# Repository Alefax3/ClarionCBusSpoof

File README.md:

# ClarionC-Blue
Clarion C-Bus interface made with arduino to spoof CD changer. Targeted use is for bluetooth, could also be simplified and used for AUX IN. The end goal is to have a single package Bluetooth module that plugs in to the CD Changer cable in the trunk and provides plug and play for bluetooth audio from a mobile phone or music device.

### Support

Testing and initial application being done in a 1995 Saab 900 S with stock head unit and existing CD changer wiring. Will work with any new generation Saab 900 from 1994 to 1998 (Excluding 1994 convertible).

Theory indicates that this unit, when assembled, will work with any Clarion made stereo using the 13 pin DIN connector as a CD changer interface. I do not have the ability to test with any other units. The only unit available to me, and the only unit I target, is the factory Clarion unit installed in my Saab 900.

This device is not planned at this time to support bluetooth hands free. It will only support A2DP (stereo audio) and AVRCP (playback controls).

The first prototype of the device will display mock track time on display, and persistent CD 1 TRACK 1, but it will not display track information. That is in the wish list, but the main goal here first is to establish communications between the device and the head unit.

### Documentation
http://embedded-bg.com/clarion_c-bus.txt

This document was incredibly insightful in regards to the protocols Clarion is using to communicate between the head and changer.

### Components
Component list will be published when a prototype has been built.

### Licensing
OPEN SOURCE BABY.

GNU General Public License, version 2.0 (GPL-2.0)

https://opensource.org/licenses/GPL-2.0

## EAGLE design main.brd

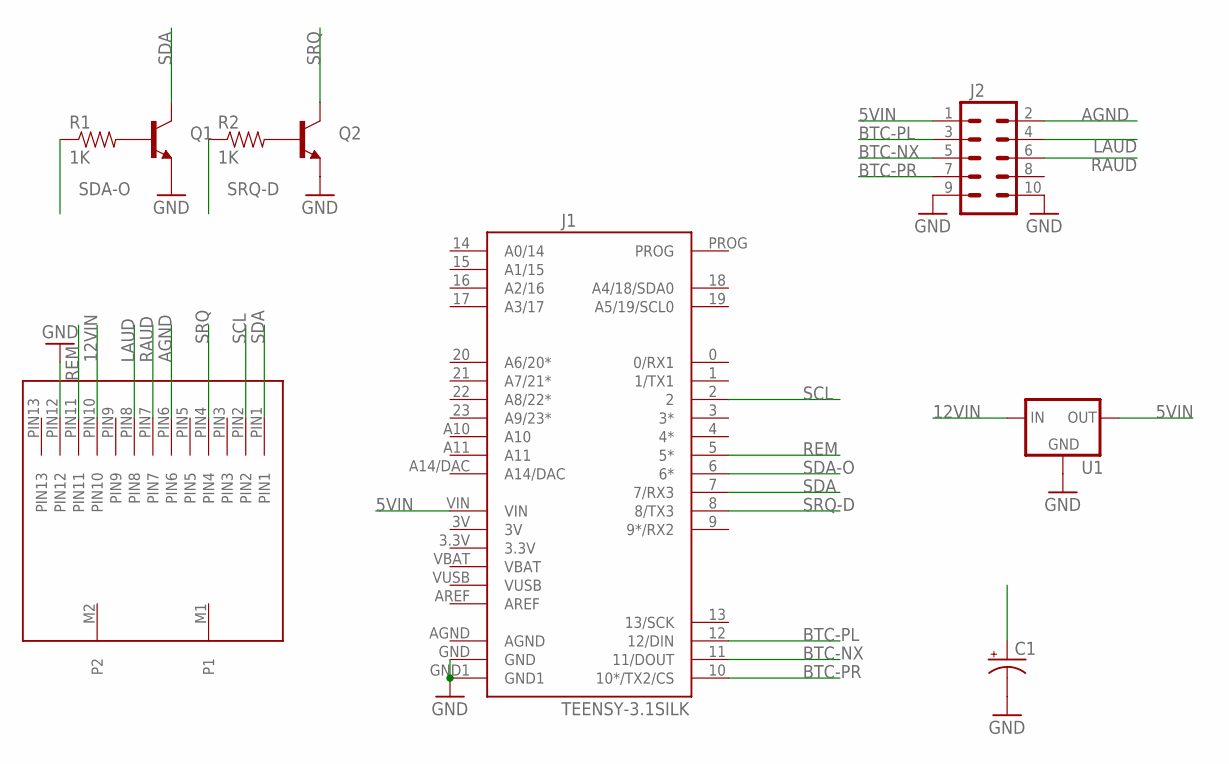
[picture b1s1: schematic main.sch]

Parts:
C1: 10UF-25V-20%(PTH); CPOL-RADIAL-10UF-25V
J1: TEENSY-3.1SILK; TEENSY-3.1
J2: M05X2NO_SILK; 2X5_NOSILK
Q1, Q2: TRANSISTOR_NPN2N3904; TO-92
R1, R2: 1K; AXIAL-0.3
U1: V_REG_78XX-TO-220; TO-220-ALT
U$1: 13-DIN13PINDIN; DIN-13

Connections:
5VIN: C1.1 (+), J1.VIN, J2.1, U1.OUT
12VIN: U1.IN, U$1.PIN10
AGND: J2.2, U$1.PIN6
BTC-NX: J1.11 (11/DOUT), J2.5
BTC-PL: J1.12 (12/DIN), J2.3
BTC-PR: J1.10 (10*/TX2/CS), J2.7
GND: C1.2 (-), J1.GND, J1.GND1, J2.9, J2.10, Q1.1 (E), Q2.1 (E), U1.GND, U$1.PIN12
LAUD: J2.4, U$1.PIN8
unnamed: Q1.2 (B), R1.P$2 (2)
unnamed: Q2.2 (B), R2.P$2 (2)
RAUD: J2.6, U$1.PIN7
REM: J1.5 (5*), U$1.PIN11
SCL: J1.2, U$1.PIN2
SDA: J1.7 (7/RX3), Q1.3 (C), U$1.PIN1
SDA-O: J1.6 (6*), R1.P$1 (1)
SRQ: Q2.3 (C), U$1.PIN4
SRQ-D: J1.8 (8/TX3), R2.P$1 (1)

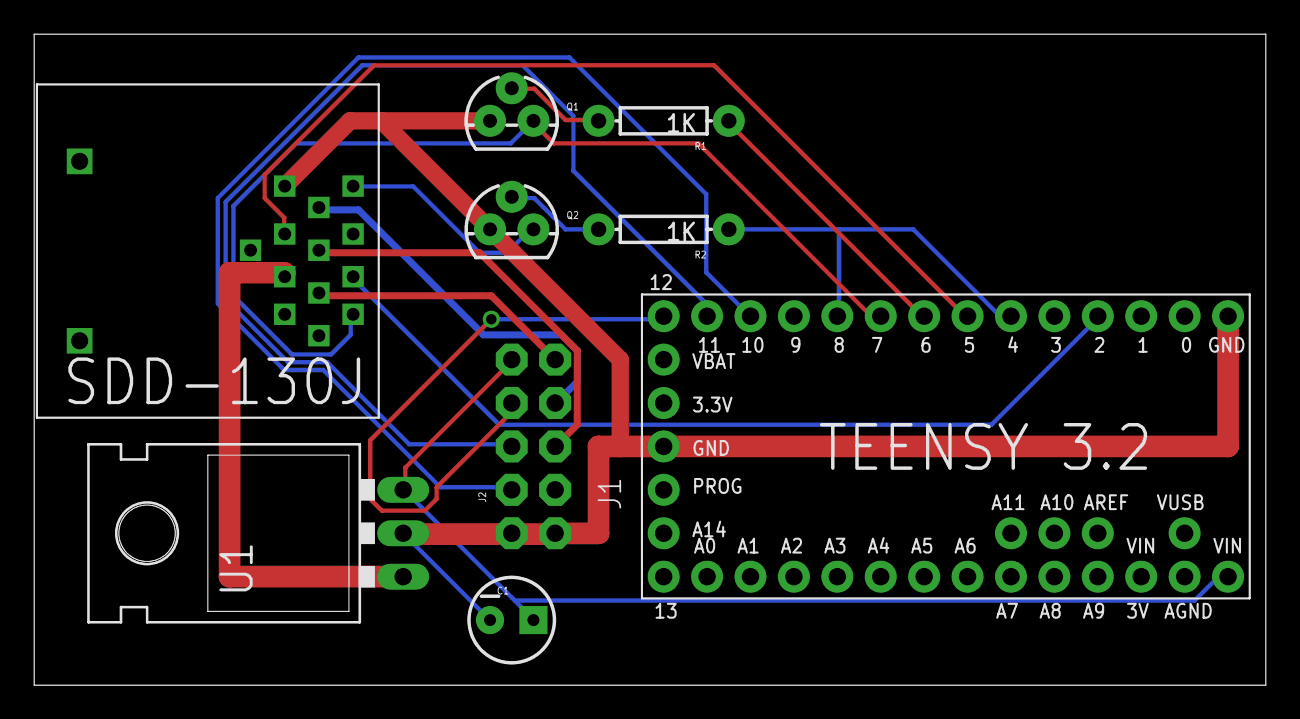
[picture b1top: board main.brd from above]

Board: 2 copper layers, 72.1 x 38.1 mm, 9 parts (0 on the bottom side), 17 nets.

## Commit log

2016-03-17 Create ClarionMain
    Initial commit of first version of code.
2016-03-17 Put slave address in variable
2016-03-17 Added PCB files
    These are still in development.
2016-03-18 Update ClarionMain
    Added serial command invocation.
2016-04-01 Added files via upload

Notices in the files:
parts and their libraries:
SparkFun-Boards: Licensing: Creative Commons ShareAlike 4.0 International - https://creativecommons.org/licenses/by-sa/4.0
